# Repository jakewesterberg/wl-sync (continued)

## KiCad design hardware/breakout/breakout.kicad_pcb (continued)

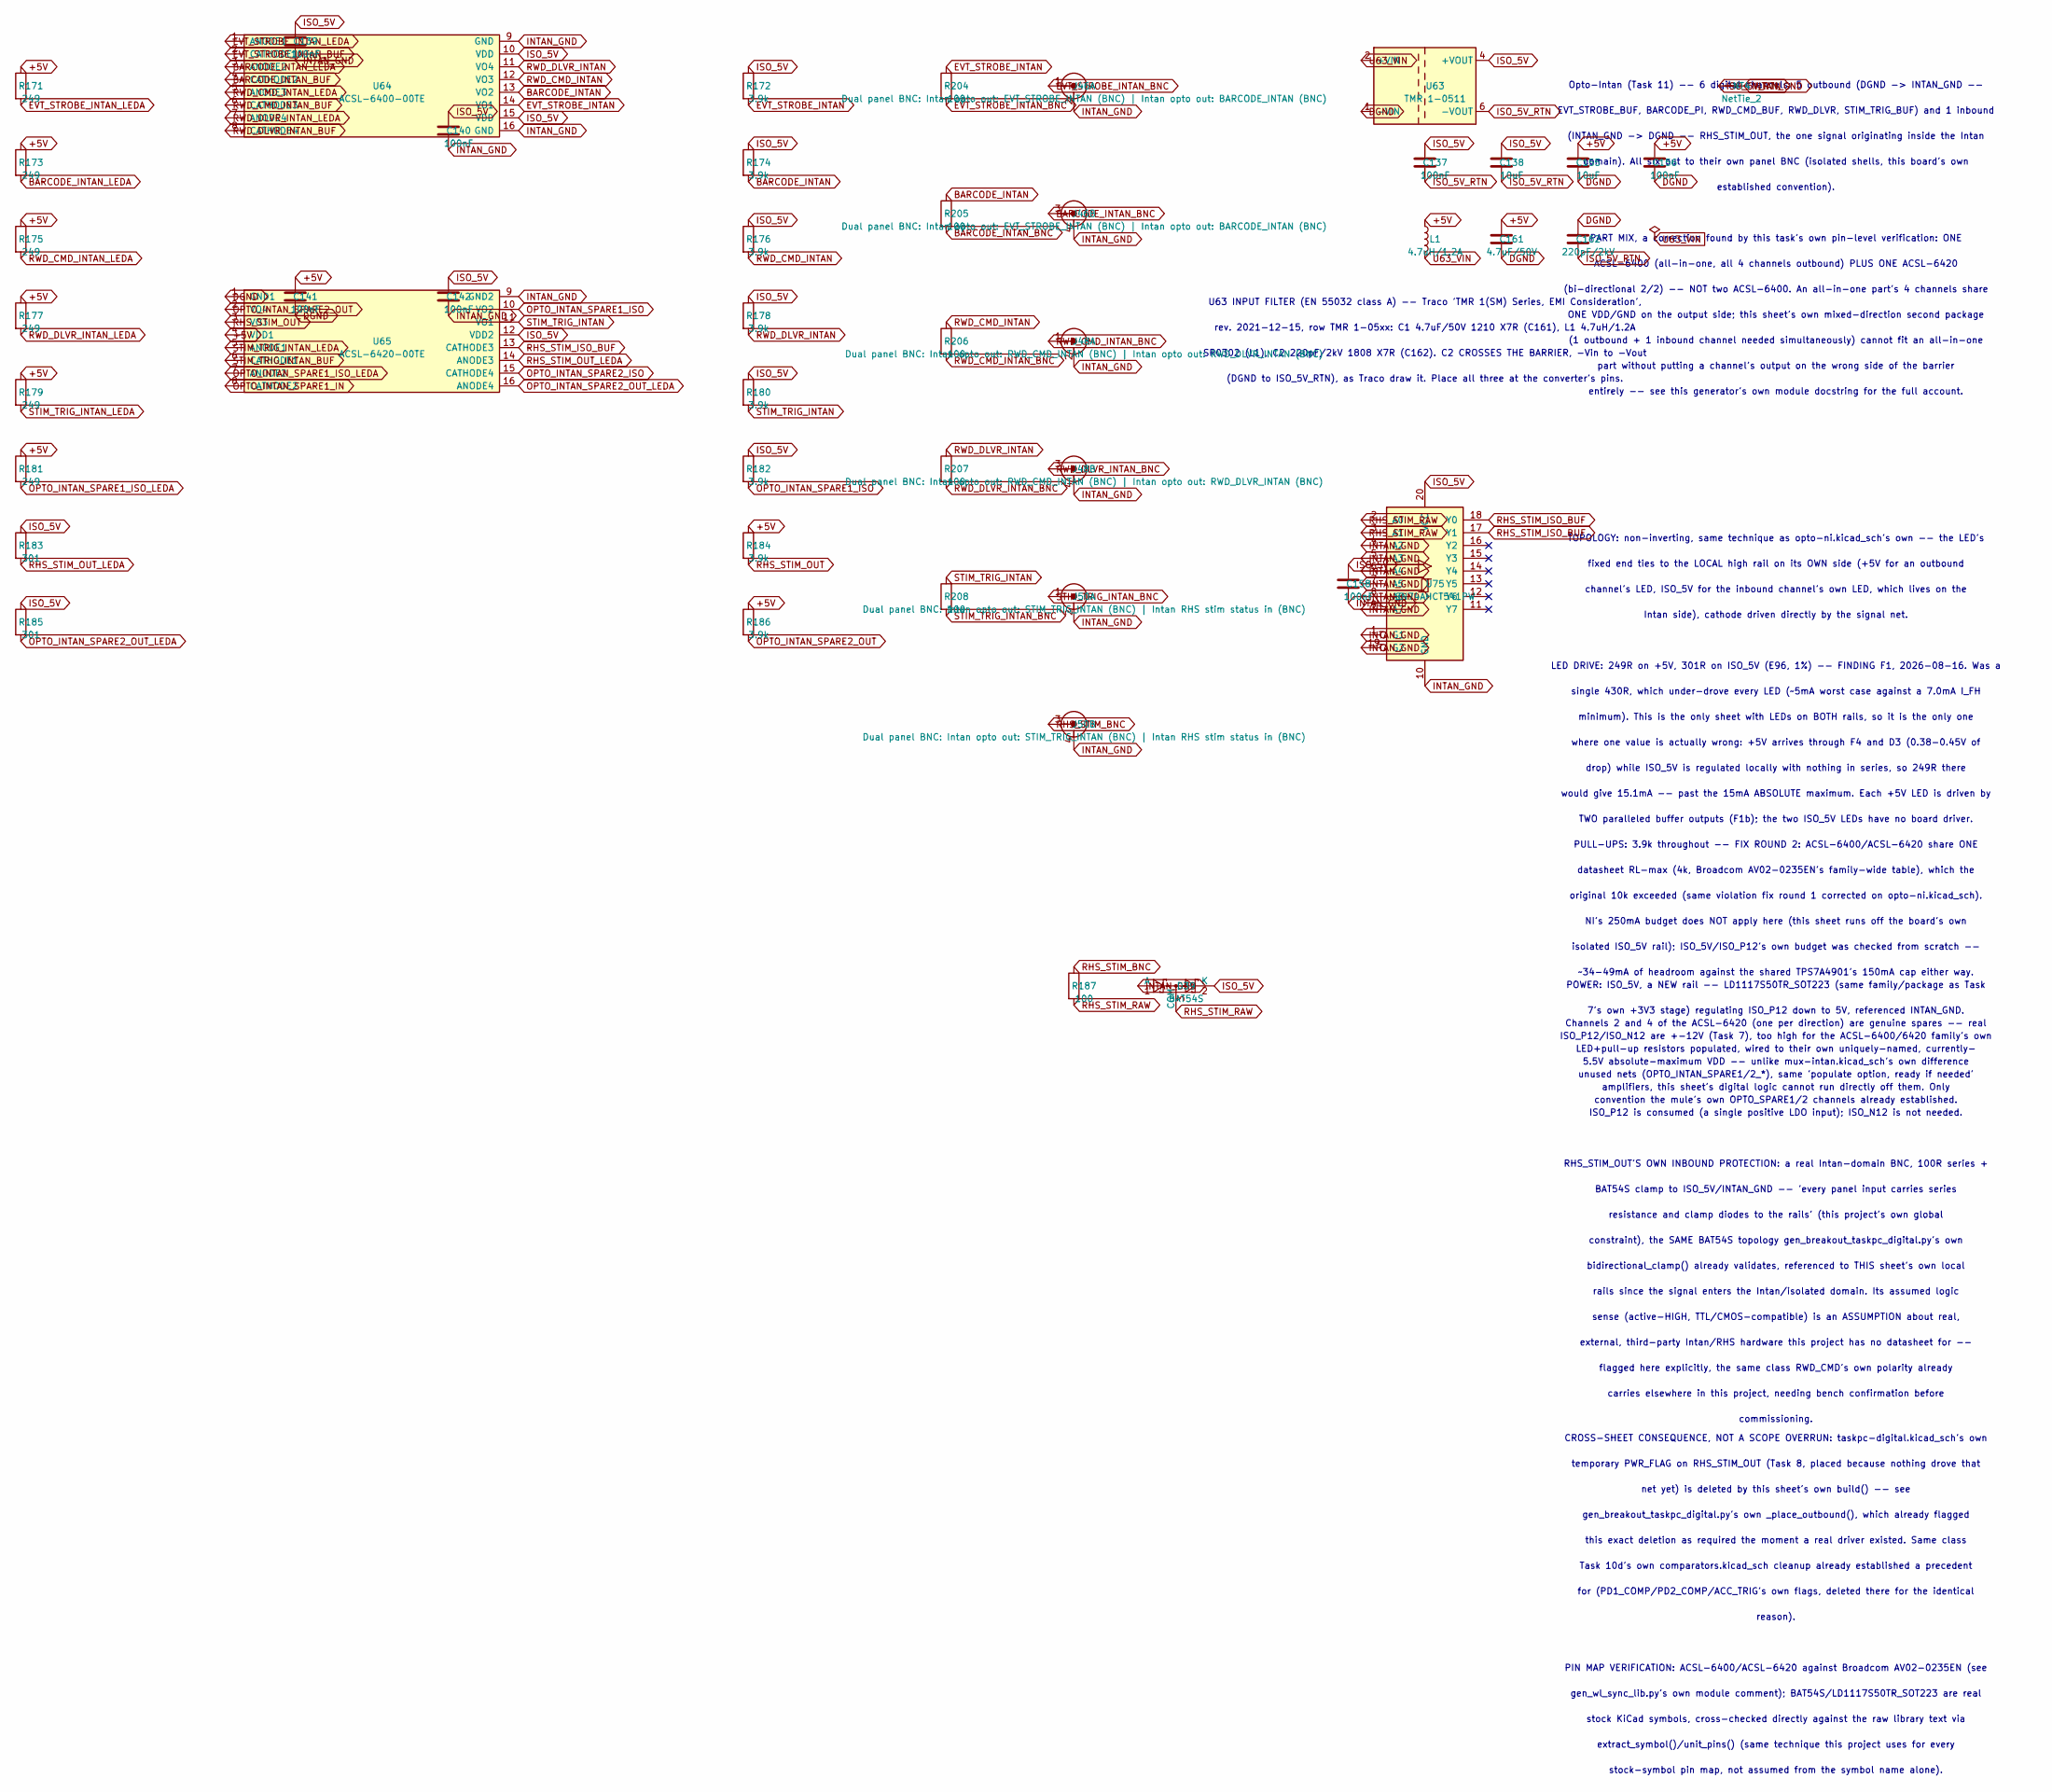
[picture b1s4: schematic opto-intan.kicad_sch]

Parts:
C137, C139, C140, C141, C142, C156, C158: 100nF; C_0603_1608Metric
C138, C155: 10uF; C_1206_3216Metric
C161: 4.7uF/50V; C_1210_3225Metric
C162: 220pF/2kV; C_1808_4520Metric
D39: BAT54S; SOT-23
J46: Dual panel BNC: Intan opto out: EVT_STROBE_INTAN 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; BNC_Dual_RA_Isolated
J48: Dual panel BNC: Intan opto out: RWD_CMD_INTAN (BN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; BNC_Dual_RA_Isolated
J50: Dual panel BNC: Intan opto out: STIM_TRIG_INTAN (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; BNC_Dual_RA_Isolated
L1: 4.7uH/1.2A; L_Ferrocore_DLG-0302
NT4: NetTie_2; NetTie-2_SMD_Pad2.0mm
R171, R173, R175, R177, R179, R181: 249; R_0603_1608Metric
R172, R174, R176, R178, R180, R182, R184, R186: 3.9k; R_0603_1608Metric
R183, R185: 301; R_0603_1608Metric
R187, R204, R205, R206, R207, R208: 100; R_0603_1608Metric
U63: TMR 1-0511; Converter_DCDC_TRACO_TMR-1-xxxx_Single_THT
U64: ACSL-6400-00TE; SOIC-16_3.9x9.9mm_P1.27mm
U65: ACSL-6420-00TE; SOIC-16_3.9x9.9mm_P1.27mm
U75: SN74AHCT541PW; Texas_PW0020A_TSSOP-20_4.4x6.5mm_P0.65mm

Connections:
BARCODE_INTAN: R174.2, R205.1, U64.13 (VO2)
BARCODE_INTAN_BNC: J46.3 (B_In), R205.2
BARCODE_INTAN_BUF: U64.4 (CATHODE2); also elsewhere on the board
BARCODE_INTAN_LEDA: R173.2, U64.3 (ANODE2)
EVT_STROBE_INTAN: R172.2, R204.1, U64.14 (VO1)
EVT_STROBE_INTAN_BNC: J46.1 (A_In), R204.2
EVT_STROBE_INTAN_BUF: U64.2 (CATHODE1); also elsewhere on the board
EVT_STROBE_INTAN_LEDA: R171.2, U64.1 (ANODE1)
INTAN_GND: C139.2, C140.2, C142.2, C158.2, D39.1 (A), J46.2 (A_Ext), J46.4 (B_Ext), J48.2 (A_Ext), J48.4 (B_Ext), J50.2 (A_Ext), J50.4 (B_Ext), NT4.2, U64.9 (GND), U64.16 (GND), U65.9 (GND2), U75.1 (G1), U75.4 (A2), U75.5 (A3), U75.6 (A4), U75.7 (A5), U75.8 (A6), U75.9 (A7), U75.10 (GND), U75.19 (G2); also elsewhere on the board
ISO_5V: C137.1, C138.1, C139.1, C140.1, C142.1, C158.1, D39.2 (K), R172.1, R174.1, R176.1, R178.1, R180.1, R182.1, R183.1, R185.1, U63.4 (+VOUT), U64.10 (VDD), U64.15 (VDD), U65.12 (VDD2), U75.20 (VCC)
ISO_5V_RTN: C137.2, C138.2, C162.2, NT4.1, U63.6 (-VOUT)
OPTO_INTAN_SPARE1_IN: U65.8 (CATHODE2)
OPTO_INTAN_SPARE1_ISO: R182.2, U65.10 (VO2)
OPTO_INTAN_SPARE1_ISO_LEDA: R181.2, U65.7 (ANODE2)
OPTO_INTAN_SPARE2_ISO: U65.15 (CATHODE4)
OPTO_INTAN_SPARE2_OUT: R186.2, U65.2 (VO4)
OPTO_INTAN_SPARE2_OUT_LEDA: R185.2, U65.16 (ANODE4)
RHS_STIM_BNC: J50.3 (B_In), R187.1
RHS_STIM_ISO_BUF: U65.13 (CATHODE3), U75.17 (Y1), U75.18 (Y0)
RHS_STIM_OUT: R184.2, U65.3 (VO3); also elsewhere on the board
RHS_STIM_OUT_LEDA: R183.2, U65.14 (ANODE3)
RHS_STIM_RAW: D39.3 (COM), R187.2, U75.2 (A0), U75.3 (A1)
RWD_CMD_INTAN: R176.2, R206.1, U64.12 (VO3)
RWD_CMD_INTAN_BNC: J48.1 (A_In), R206.2
RWD_CMD_INTAN_BUF: U64.6 (CATHODE3); also elsewhere on the board
RWD_CMD_INTAN_LEDA: R175.2, U64.5 (ANODE3)
RWD_DLVR_INTAN: R178.2, R207.1, U64.11 (VO4)
RWD_DLVR_INTAN_BNC: J48.3 (B_In), R207.2
RWD_DLVR_INTAN_BUF: U64.8 (CATHODE4); also elsewhere on the board
RWD_DLVR_INTAN_LEDA: R177.2, U64.7 (ANODE4)
STIM_TRIG_INTAN: R180.2, R208.1, U65.11 (VO1)
STIM_TRIG_INTAN_BNC: J50.1 (A_In), R208.2
STIM_TRIG_INTAN_BUF: U65.6 (CATHODE1); also elsewhere on the board
STIM_TRIG_INTAN_LEDA: R179.2, U65.5 (ANODE1)
U63_VIN: L1.2, U63.2 (+VIN)

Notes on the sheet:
extract_symbol()/unit_pins() (same technique this project uses for every
minimum). This is the only sheet with LEDs on BOTH rails, so it is the only one
ISO_P12/ISO_N12 are +-12V (Task 7), too high for the ACSL-6400/6420 family's own
rev. 2021-12-15, row TMR 1-05xx: C1 4.7uF/50V 1210 X7R (C161), L1 4.7uH/1.2A
entirely -- see this generator's own module docstring for the full account.
Opto-Intan (Task 11) -- 6 digital channels: 5 outbound (DGND -> INTAN_GND --
established convention).
resistance and clamp diodes to the rails' (this project's own global
domain). All six out to their own panel BNC (isolated shells, this board's own
(bi-directional 2/2) -- NOT two ACSL-6400. An all-in-one part's 4 channels share
carries elsewhere in this project, needing bench confirmation before
LED+pull-up resistors populated, wired to their own uniquely-named, currently-
TWO paralleled buffer outputs (F1b); the two ISO_5V LEDs have no board driver.
this exact deletion as required the moment a real driver existed. Same class
convention the mule's own OPTO_SPARE1/2 channels already established.
temporary PWR_FLAG on RHS_STIM_OUT (Task 8, placed because nothing drove that
Channels 2 and 4 of the ACSL-6420 (one per direction) are genuine spares -- real
PIN MAP VERIFICATION: ACSL-6400/ACSL-6420 against Broadcom AV02-0235EN (see
single 430R, which under-drove every LED (~5mA worst case against a 7.0mA I_FH
external, third-party Intan/RHS hardware this project has no datasheet for --
7's own +3V3 stage) regulating ISO_P12 down to 5V, referenced INTAN_GND.
BAT54S clamp to ISO_5V/INTAN_GND -- 'every panel input carries series
datasheet RL-max (4k, Broadcom AV02-0235EN's family-wide table), which the
sense (active-HIGH, TTL/CMOS-compatible) is an ASSUMPTION about real,
original 10k exceeded (same violation fix round 1 corrected on opto-ni.kicad_sch).
bidirectional_clamp() already validates, referenced to THIS sheet's own local
~34-49mA of headroom against the shared TPS7A4901's 150mA cap either way.
unused nets (OPTO_INTAN_SPARE1/2_*), same 'populate option, ready if needed'
net yet) is deleted by this sheet's own build() -- see
5.5V absolute-maximum VDD -- unlike mux-intan.kicad_sch's own difference
LED DRIVE: 249R on +5V, 301R on ISO_5V (E96, 1%) -- FINDING F1, 2026-08-16. Was a
amplifiers, this sheet's digital logic cannot run directly off them. Only
POWER: ISO_5V, a NEW rail -- LD1117S50TR_SOT223 (same family/package as Task
ONE VDD/GND on the output side; this sheet's own mixed-direction second package
PART MIX, a correction found by this task's own pin-level verification: ONE
isolated ISO_5V rail); ISO_5V/ISO_P12's own budget was checked from scratch --
(1 outbound + 1 inbound channel needed simultaneously) cannot fit an all-in-one
Task 10d's own comparators.kicad_sch cleanup already established a precedent
gen_wl_sync_lib.py's own module comment); BAT54S/LD1117S50TR_SOT223 are real
fixed end ties to the LOCAL high rail on its OWN side (+5V for an outbound

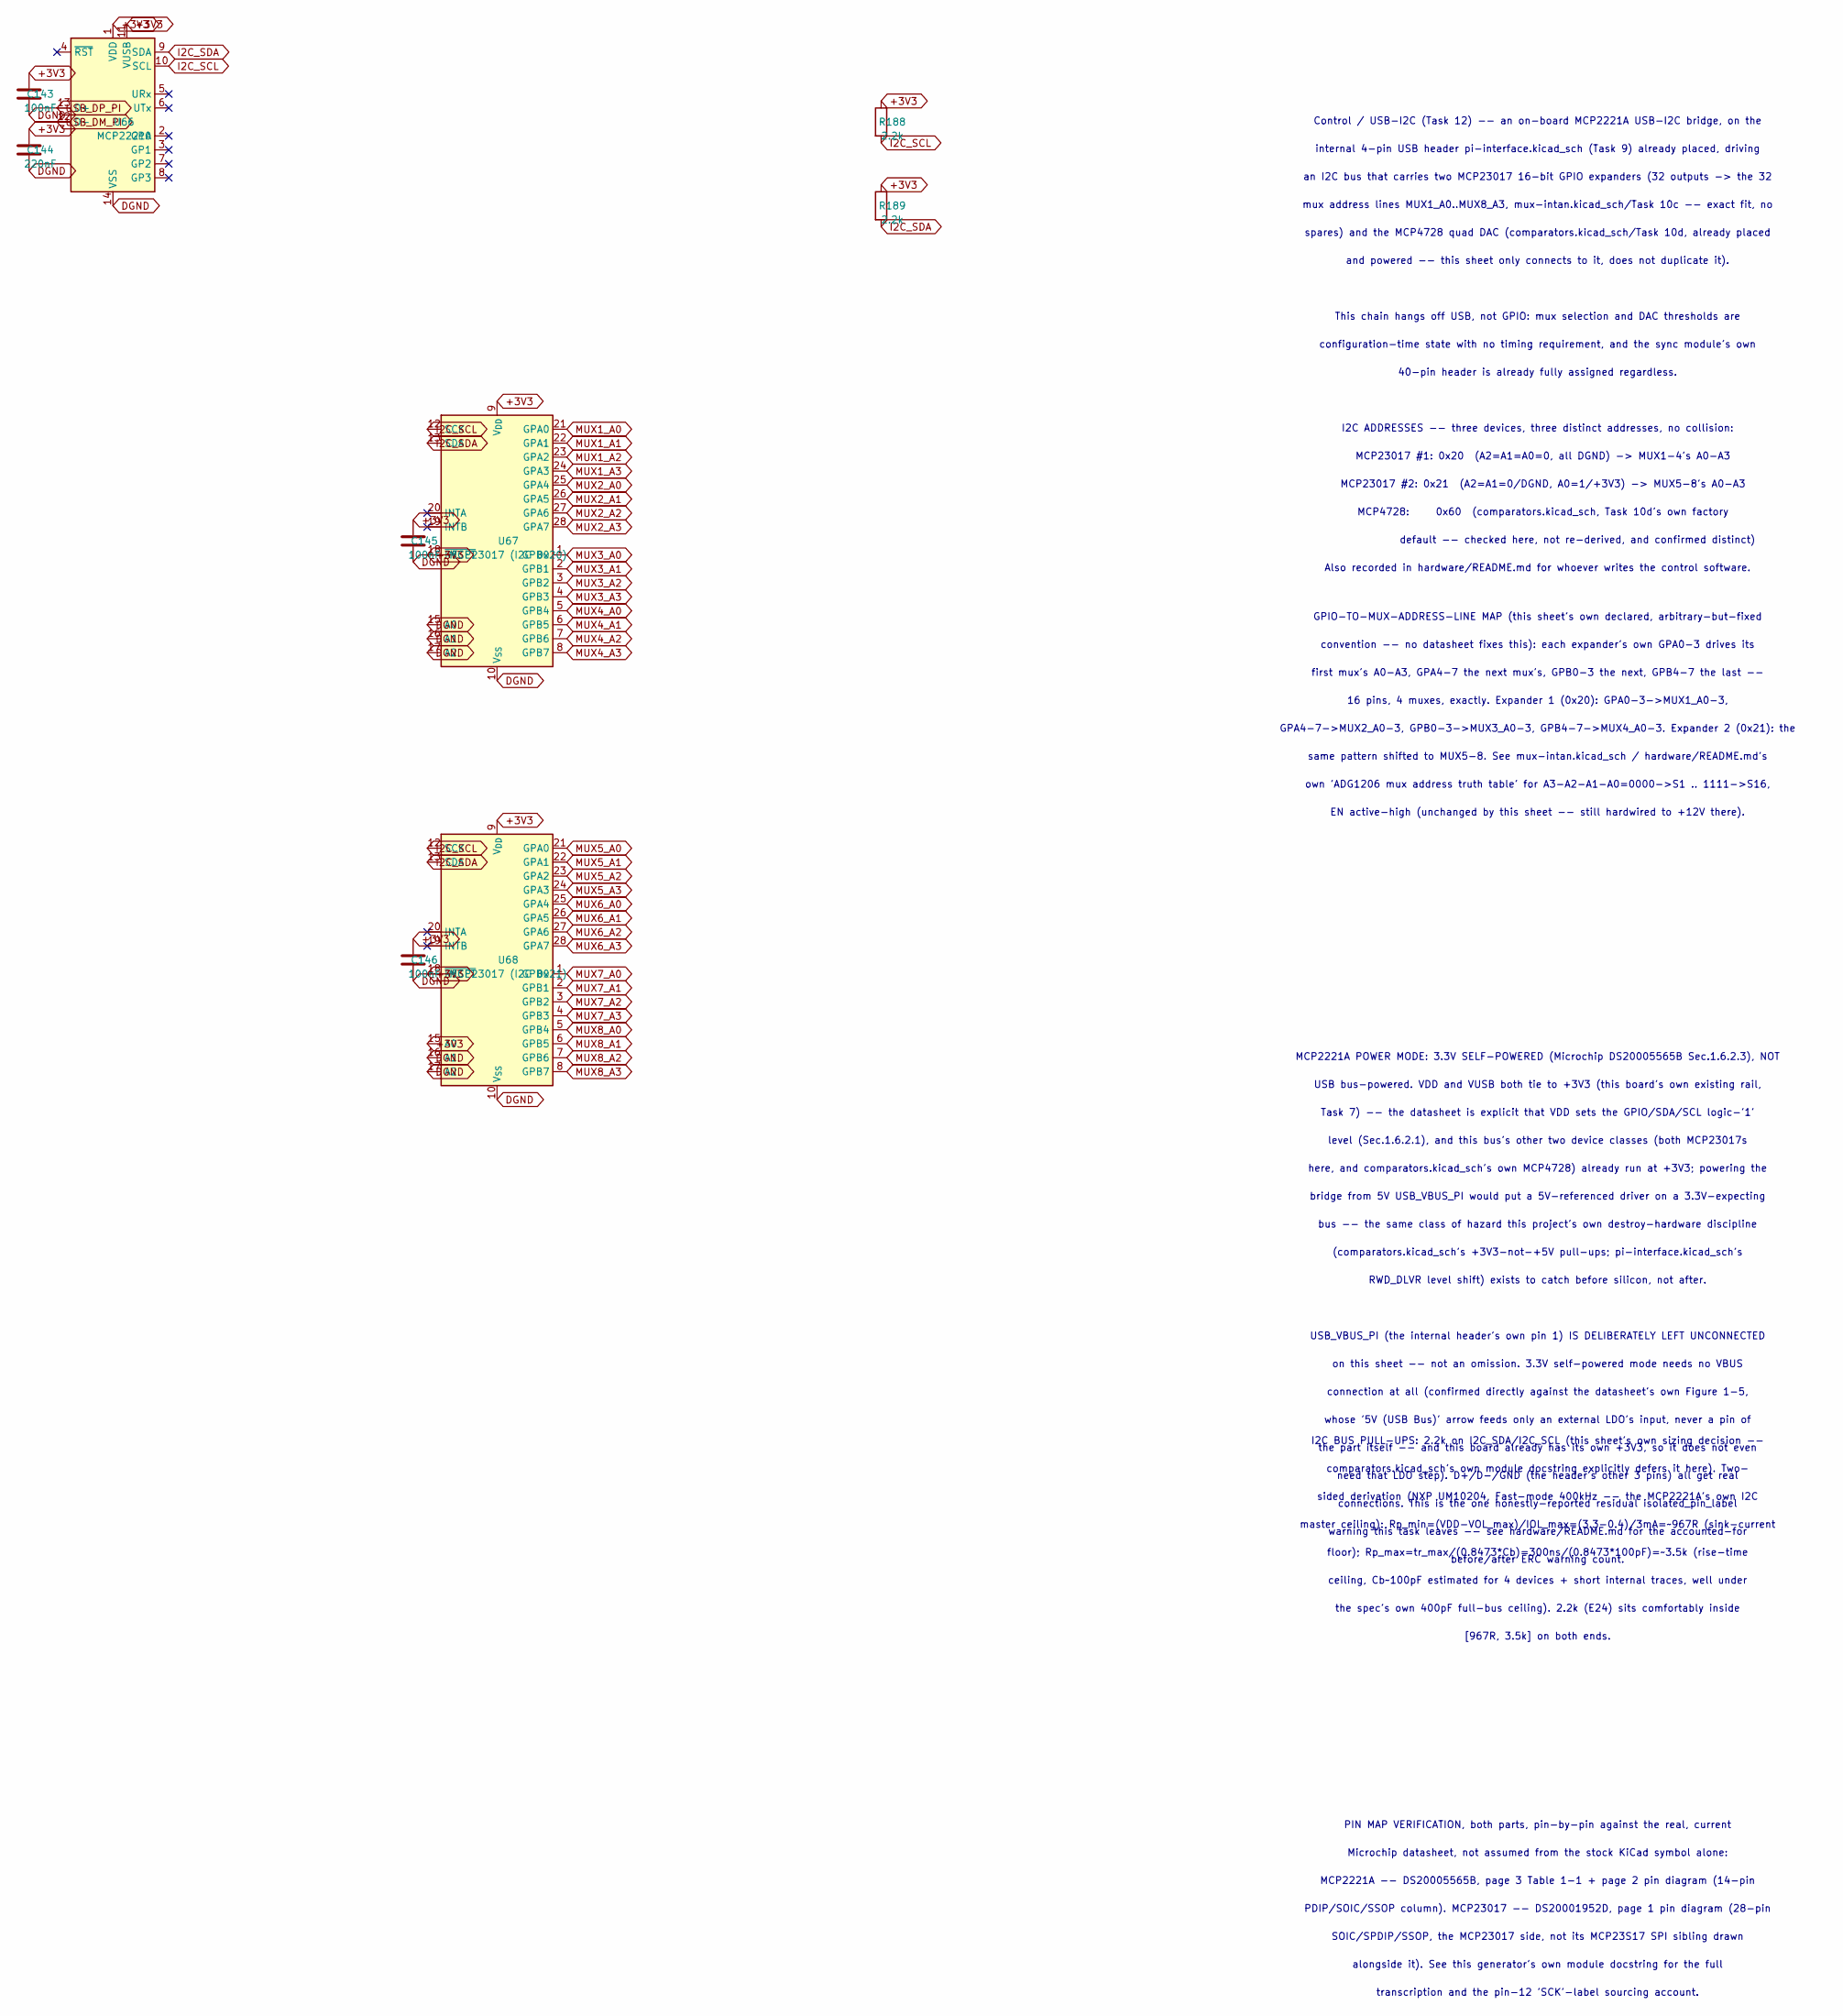
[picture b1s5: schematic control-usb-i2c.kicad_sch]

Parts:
C143, C145, C146: 100nF; C_0603_1608Metric
C144: 220nF; C_0603_1608Metric
R188, R189: 2.2k; R_0603_1608Metric
U66: MCP2221A; SOIC-14_3.9x8.7mm_P1.27mm
U67: MCP23017 (I2C 0x20); SOIC-28W_7.5x17.9mm_P1.27mm
U68: MCP23017 (I2C 0x21); SOIC-28W_7.5x17.9mm_P1.27mm

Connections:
+3V3: C143.1, C144.1, C145.1, C146.1, R188.1, R189.1, U66.1 (VDD), U66.11 (VUSB), U67.9 (V_{DD}), U67.18 (~RESET), U68.9 (V_{DD}), U68.15 (A0), U68.18 (~RESET); also elsewhere on the board
I2C_SCL: R188.2, U66.10 (SCL), U67.12 (SCK), U68.12 (SCK); also elsewhere on the board
I2C_SDA: R189.2, U66.9 (SDA), U67.13 (SDA), U68.13 (SDA); also elsewhere on the board
MUX1_A0: U67.21 (GPA0); also elsewhere on the board
MUX1_A1: U67.22 (GPA1); also elsewhere on the board
MUX1_A2: U67.23 (GPA2); also elsewhere on the board
MUX1_A3: U67.24 (GPA3); also elsewhere on the board
MUX2_A0: U67.25 (GPA4); also elsewhere on the board
MUX2_A1: U67.26 (GPA5); also elsewhere on the board
MUX2_A2: U67.27 (GPA6); also elsewhere on the board
MUX2_A3: U67.28 (GPA7); also elsewhere on the board
MUX3_A0: U67.1 (GPB0); also elsewhere on the board
MUX3_A1: U67.2 (GPB1); also elsewhere on the board
MUX3_A2: U67.3 (GPB2); also elsewhere on the board
MUX3_A3: U67.4 (GPB3); also elsewhere on the board
MUX4_A0: U67.5 (GPB4); also elsewhere on the board
MUX4_A1: U67.6 (GPB5); also elsewhere on the board
MUX4_A2: U67.7 (GPB6); also elsewhere on the board
MUX4_A3: U67.8 (GPB7); also elsewhere on the board
MUX5_A0: U68.21 (GPA0); also elsewhere on the board
MUX5_A1: U68.22 (GPA1); also elsewhere on the board
MUX5_A2: U68.23 (GPA2); also elsewhere on the board
MUX5_A3: U68.24 (GPA3); also elsewhere on the board
MUX6_A0: U68.25 (GPA4); also elsewhere on the board
MUX6_A1: U68.26 (GPA5); also elsewhere on the board
MUX6_A2: U68.27 (GPA6); also elsewhere on the board
MUX6_A3: U68.28 (GPA7); also elsewhere on the board
MUX7_A0: U68.1 (GPB0); also elsewhere on the board
MUX7_A1: U68.2 (GPB1); also elsewhere on the board
MUX7_A2: U68.3 (GPB2); also elsewhere on the board
MUX7_A3: U68.4 (GPB3); also elsewhere on the board
MUX8_A0: U68.5 (GPB4); also elsewhere on the board
MUX8_A1: U68.6 (GPB5); also elsewhere on the board
MUX8_A2: U68.7 (GPB6); also elsewhere on the board
MUX8_A3: U68.8 (GPB7); also elsewhere on the board
USB_DM_PI: U66.12 (D-); also elsewhere on the board
USB_DP_PI: U66.13 (D+); also elsewhere on the board

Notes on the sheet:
Control / USB-I2C (Task 12) -- an on-board MCP2221A USB-I2C bridge, on the
internal 4-pin USB header pi-interface.kicad_sch (Task 9) already placed, driving
an I2C bus that carries two MCP23017 16-bit GPIO expanders (32 outputs -> the 32
mux address lines MUX1_A0..MUX8_A3, mux-intan.kicad_sch/Task 10c -- exact fit, no
spares) and the MCP4728 quad DAC (comparators.kicad_sch/Task 10d, already placed
and powered -- this sheet only connects to it, does not duplicate it).
This chain hangs off USB, not GPIO: mux selection and DAC thresholds are
configuration-time state with no timing requirement, and the sync module's own
40-pin header is already fully assigned regardless.
I2C ADDRESSES -- three devices, three distinct addresses, no collision:
MCP23017 #1: 0x20 (A2=A1=A0=0, all DGND) -> MUX1-4's A0-A3
MCP23017 #2: 0x21 (A2=A1=0/DGND, A0=1/+3V3) -> MUX5-8's A0-A3
MCP4728: 0x60 (comparators.kicad_sch, Task 10d's own factory
default -- checked here, not re-derived, and confirmed distinct)
Also recorded in hardware/README.md for whoever writes the control software.
GPIO-TO-MUX-ADDRESS-LINE MAP (this sheet's own declared, arbitrary-but-fixed
convention -- no datasheet fixes this): each expander's own GPA0-3 drives its
first mux's A0-A3, GPA4-7 the next mux's, GPB0-3 the next, GPB4-7 the last --
16 pins, 4 muxes, exactly. Expander 1 (0x20): GPA0-3->MUX1_A0-3,
GPA4-7->MUX2_A0-3, GPB0-3->MUX3_A0-3, GPB4-7->MUX4_A0-3. Expander 2 (0x21): the
same pattern shifted to MUX5-8. See mux-intan.kicad_sch / hardware/README.md's
own 'ADG1206 mux address truth table' for A3-A2-A1-A0=0000->S1 .. 1111->S16,
EN active-high (unchanged by this sheet -- still hardwired to +12V there).
MCP2221A POWER MODE: 3.3V SELF-POWERED (Microchip DS20005565B Sec.1.6.2.3), NOT
USB bus-powered. VDD and VUSB both tie to +3V3 (this board's own existing rail,
Task 7) -- the datasheet is explicit that VDD sets the GPIO/SDA/SCL logic-'1'
level (Sec.1.6.2.1), and this bus's other two device classes (both MCP23017s
here, and comparators.kicad_sch's own MCP4728) already run at +3V3; powering the
bridge from 5V USB_VBUS_PI would put a 5V-referenced driver on a 3.3V-expecting
bus -- the same class of hazard this project's own destroy-hardware discipline
(comparators.kicad_sch's +3V3-not-+5V pull-ups; pi-interface.kicad_sch's
RWD_DLVR level shift) exists to catch before silicon, not after.
USB_VBUS_PI (the internal header's own pin 1) IS DELIBERATELY LEFT UNCONNECTED
on this sheet -- not an omission. 3.3V self-powered mode needs no VBUS
connection at all (confirmed directly against the datasheet's own Figure 1-5,
whose '5V (USB Bus)' arrow feeds only an external LDO's input, never a pin of
the part itself -- and this board already has its own +3V3, so it does not even
need that LDO step). D+/D-/GND (the header's other 3 pins) all get real
connections. This is the one honestly-reported residual isolated_pin_label
warning this task leaves -- see hardware/README.md for the accounted-for
